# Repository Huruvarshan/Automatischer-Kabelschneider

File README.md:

# Automatischer Kabelschneider (Automatic Cable Cutter)

## Overview

The **Automatischer Kabelschneider** is an open-source, programmable device for automatically cutting cables and heat shrink tubes to precise lengths and quantities. Designed for makers, professionals, and hobbyists, it streamlines repetitive workshop tasks, ensuring accuracy, safety, and efficiency in cable and tube preparation.

This repository includes all hardware and software resources needed to build, assemble, and operate the device.

---

## Features

- **Programmable Length & Quantity:**  
  Set the desired length and number of pieces using capacitive buttons and an integrated display.

- **Precision Cutting:**  
  Delivers clean, accurate cuts suitable for various cable and tube diameters.

- **Material Flexibility:**  
  Supports cables, heat shrink tubes, and similar flexible materials.

- **Job Notification:**  
  Visual indicators (LEDs or beacons) signal job progress and completion.

- **Safety:**  
  Built-in overheat protection, a "SawStop"-style emergency system, and run-out sensors to prevent accidents.

---

## Repository Structure

```
Automatischer-Kabelschneider/
├── Hardware/
│   ├── PCB/           # KiCad PCB design files
│   ├── Mechanical/    # Mechanical design files (e.g., 3D models)
│   ├── BOM.md         # Bill of Materials
│   └── README.md      # Hardware documentation
├── Software/
│   ├── AKS_Program/   # Microcontroller firmware (ESP32)
│   │   └── README.md  # Software setup and usage
│   └── README.md      # Software structure and notes
├── Images/            # Project and schematic images
│   └── A6703971.JPG
└── README.md          # Project overview (this file)
```

---

## Getting Started

### 1. Hardware

- Manufacture and assemble the PCB and mechanical parts using files in `/Hardware`.
- Reference the Bill of Materials (`Hardware/BOM.md`) for required components.
- Follow detailed assembly instructions in `Hardware/README.md`.

### 2. Software

- The main firmware for the microcontroller (ESP32) is located in `Software/AKS_Program/`.
- See `Software/AKS_Program/README.md` for build, installation, and configuration steps.
- The firmware controls motors, sensors, and LED feedback, and communicates with the device interface.

### 3. Operation

- Use the device's capacitive interface to configure cut length and quantity.
- Start the automatic cutting process. LEDs provide real-time feedback.
- The machine stops automatically and alerts you when the job is complete.

---

## Documentation

- **Hardware Details:** [Hardware/README.md](Hardware/README.md)
- **Software Instructions:** [Software/AKS_Program/README.md](Software/AKS_Program/README.md)

---

## Contributing

Contributions, bug reports, and suggestions are welcome!  
Please open an issue or submit a pull request via GitHub.

---

## Safety & Disclaimer

- Always follow safety instructions and observe caution while operating the device.
- The authors are not responsible for any injury or damage resulting from use or misuse of this project.

---

## License

This project is licensed under the MIT License.  
See [LICENSE](LICENSE) for details.

---

**Let’s build better tools together!**

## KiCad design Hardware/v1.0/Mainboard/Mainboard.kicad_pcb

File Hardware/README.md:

# Hardware Documentation

Welcome to the hardware section of the Automatischer Kabelschneider (Automatic Cable Cutter) project.

## PCB Design

- The PCB (Printed Circuit Board) design files are available here:  
  [./PCB/](Automatischer-Kabelschneider/Hardware/PCB/)

## Mechanical Design

- The mechanical design files can be found here:  
  [./Mechanical/](../Mechanical/)  

## Bill of Materials (BOM)

- A complete list of components required for the hardware build is available here:  
  [./BOM.md](./BOM.md)  

## Assembly Instructions

- Step-by-step instructions for assembling the hardware will be provided here.  

## Firmware

- The firmware for running the device is located in the main repository:  
  [../Firmware/](../Firmware/)

## Additional Notes

- Please check that all the referenced files and folders are present in this directory.
- For troubleshooting, questions, or contributions, please open an issue in the main repository.

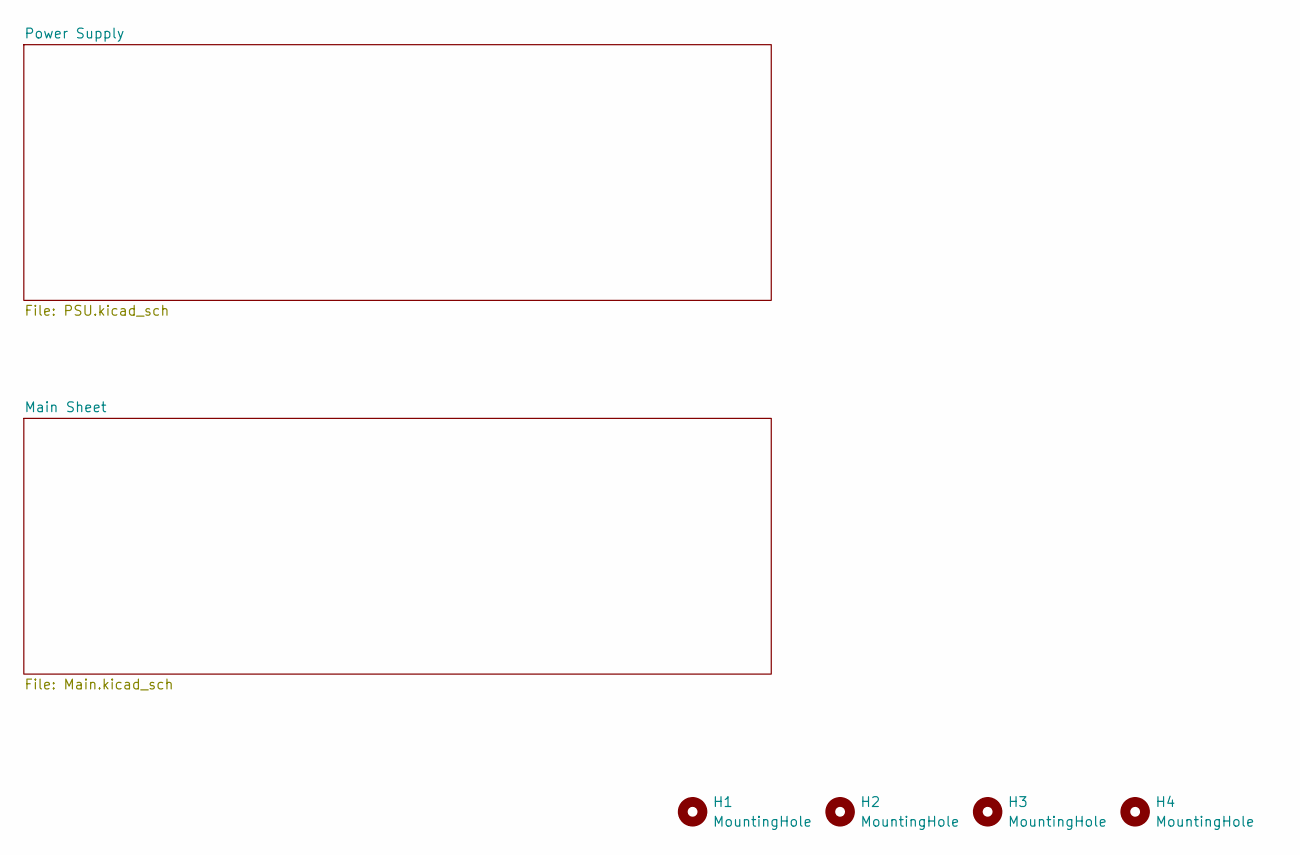
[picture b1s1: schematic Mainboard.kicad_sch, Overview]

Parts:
H1, H2, H3, H4: MountingHole; MountingHole_3.2mm_M3

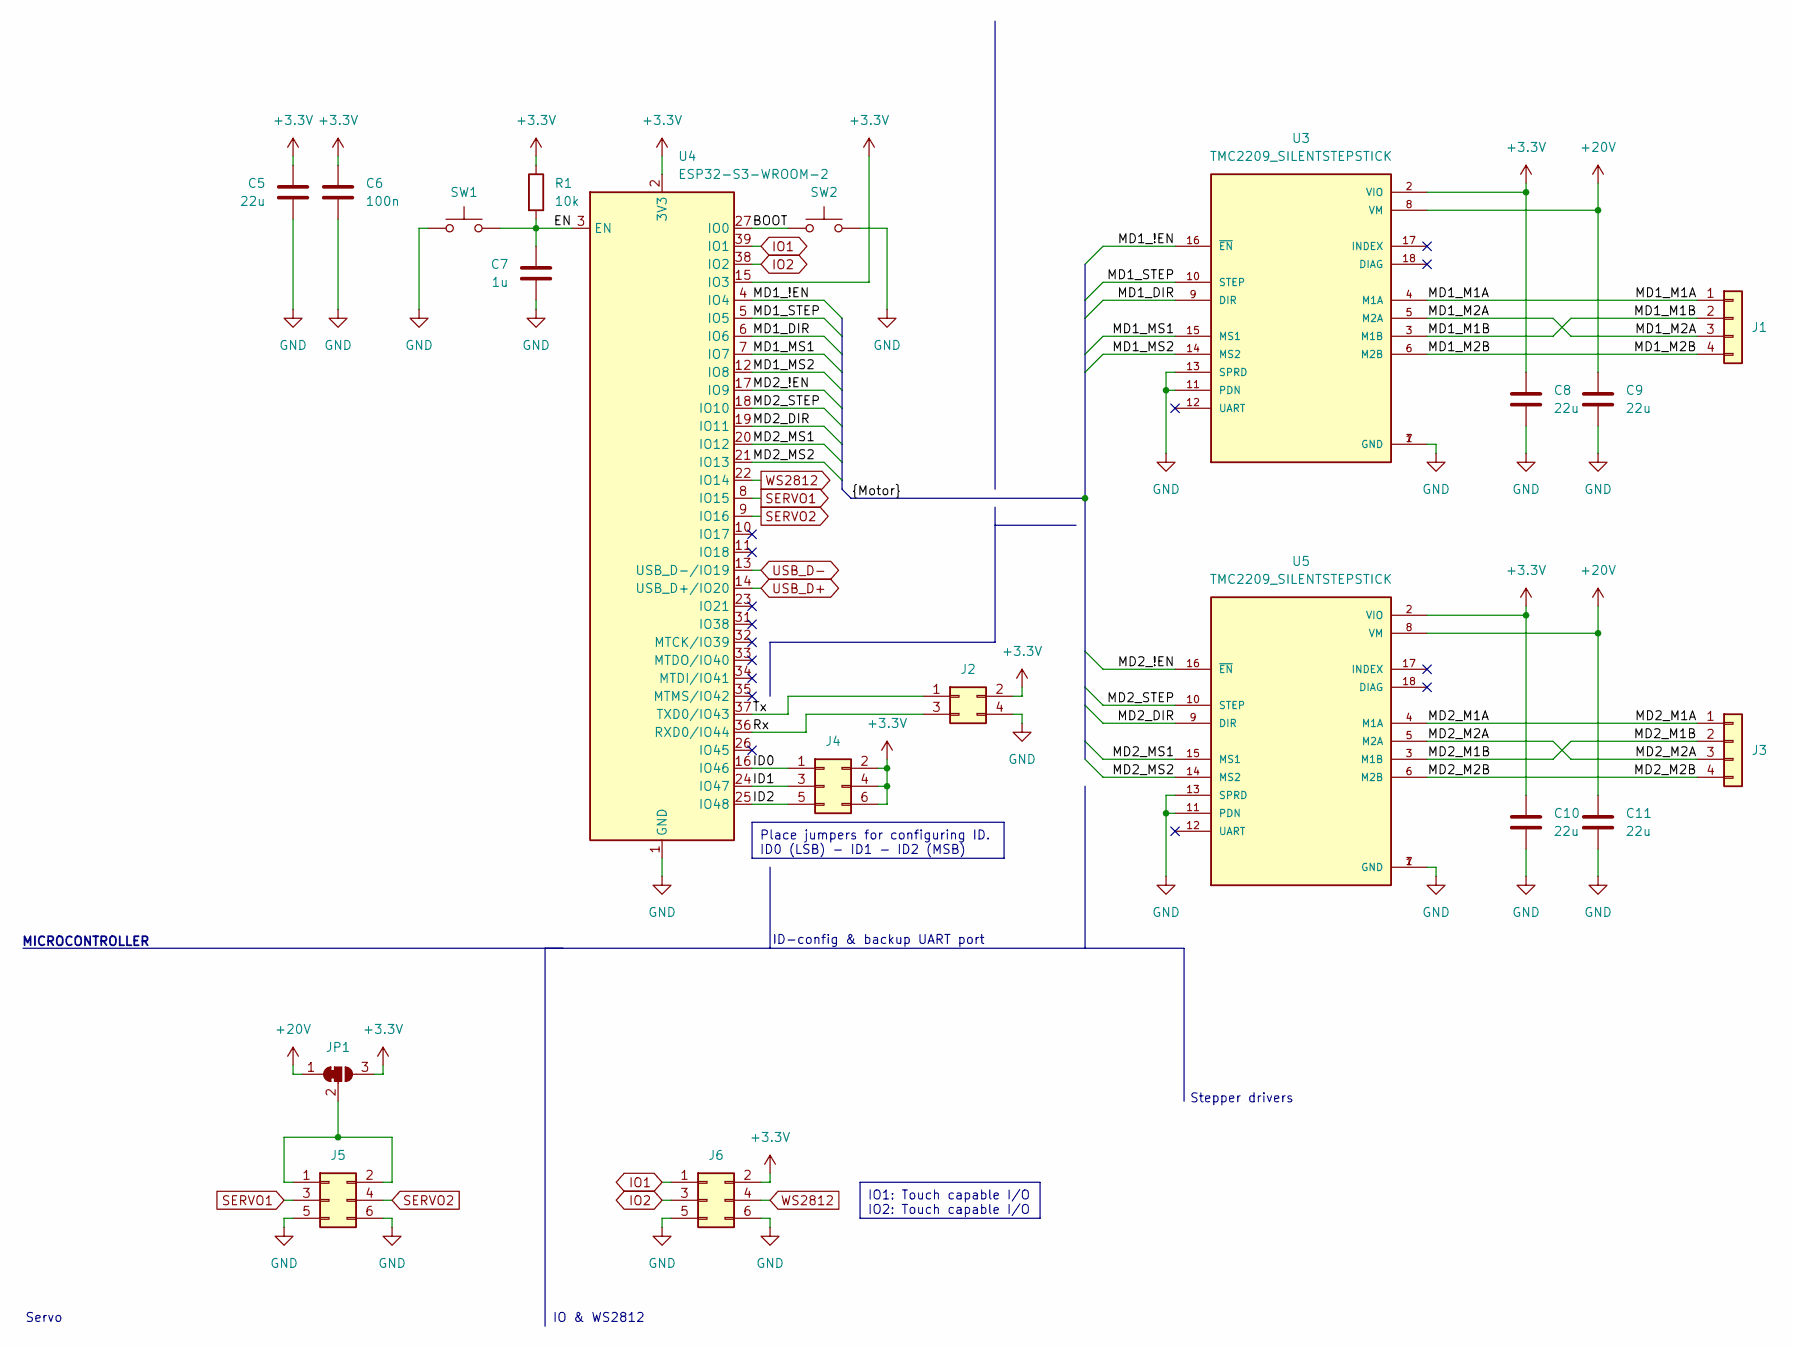
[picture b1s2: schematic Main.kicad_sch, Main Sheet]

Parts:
C5, C8, C9, C10, C11: 22u; C_0805_2012Metric
C6: 100n; C_0805_2012Metric
C7: 1u; C_0805_2012Metric
J1, J3: Conn_01x04; PhoenixContact_MC_1,5_4-G-3.81_1x04_P3.81mm_Horizontal
J2: Conn_02x02_Odd_Even; PinHeader_2x02_P2.54mm_Vertical
J4, J5, J6: Conn_02x03_Odd_Even; PinHeader_2x03_P2.54mm_Vertical
JP1: SolderJumper_3_Bridged12; SolderJumper-3_P1.3mm_Bridged12_RoundedPad1.0x1.5mm
R1: 10k; R_0805_2012Metric
SW1, SW2: SW_Push; SW_Push_1P1T_NO_6x6mm_H9.5mm
U3, U5: TMC2209_SILENTSTEPSTICK; MODULE_TMC2209_SILENTSTEPSTICK; PARTREV 1.20
U4: ESP32-S3-WROOM-2

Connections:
+3.3V: C5.1, C6.1, C8.1, C10.1, J2.2, J4.2, J4.4, J4.6, J6.2, JP1.3 (B), R1.1, U3.2 (VIO), U4.2 (3V3), U4.15 (IO3), U5.2 (VIO); also elsewhere on the board
+20V: C9.1, C11.1, JP1.1 (A), U3.8 (VM), U5.8 (VM); also elsewhere on the board
/Main Sheet/BOOT: SW2.1, U4.27 (IO0)
/Main Sheet/EN: C7.1, R1.2, SW1.2, U4.3 (EN)
/Main Sheet/ID0: J4.1, U4.16 (IO46)
/Main Sheet/ID1: J4.3, U4.24 (IO47)
/Main Sheet/ID2: J4.5, U4.25 (IO48)
/Main Sheet/MD1_!EN: U3.16 (~EN), U4.4 (IO4)
/Main Sheet/MD1_DIR: U3.9 (DIR), U4.6 (IO6)
/Main Sheet/MD1_M1A: J1.1, U3.4 (M1A)
/Main Sheet/MD1_M1B: J1.2, U3.3 (M1B)
/Main Sheet/MD1_M2A: J1.3, U3.5 (M2A)
/Main Sheet/MD1_M2B: J1.4, U3.6 (M2B)
/Main Sheet/MD1_MS1: U3.15 (MS1), U4.7 (IO7)
/Main Sheet/MD1_MS2: U3.14 (MS2), U4.12 (IO8)
/Main Sheet/MD1_STEP: U3.10 (STEP), U4.5 (IO5)
/Main Sheet/MD2_!EN: U4.17 (IO9), U5.16 (~EN)
/Main Sheet/MD2_DIR: U4.19 (IO11), U5.9 (DIR)
/Main Sheet/MD2_M1A: J3.1, U5.4 (M1A)
/Main Sheet/MD2_M1B: J3.2, U5.3 (M1B)
/Main Sheet/MD2_M2A: J3.3, U5.5 (M2A)
/Main Sheet/MD2_M2B: J3.4, U5.6 (M2B)
/Main Sheet/MD2_MS1: U4.20 (IO12), U5.15 (MS1)
/Main Sheet/MD2_MS2: U4.21 (IO13), U5.14 (MS2)
/Main Sheet/MD2_STEP: U4.18 (IO10), U5.10 (STEP)
/Main Sheet/Rx: J2.3, U4.36 (RXD0/IO44)
/Main Sheet/Tx: J2.1, U4.37 (TXD0/IO43)
GND: C5.2, C6.2, C7.2, C8.2, C9.2, C10.2, C11.2, J2.4, J5.5, J5.6, J6.5, J6.6, SW1.1, SW2.2, U3.1 (GND), U3.7 (GND), U3.11 (PDN), U3.13 (SPRD), U4.1 (GND), U4.40 (GND), U4.41 (GND), U5.1 (GND), U5.7 (GND), U5.11 (PDN), U5.13 (SPRD); also elsewhere on the board
IO1: J6.1, U4.39 (IO1)
IO2: J6.3, U4.38 (IO2)
unnamed: J5.1, J5.2, JP1.2 (C)
SERVO1: J5.3, U4.8 (IO15)
SERVO2: J5.4, U4.9 (IO16)
USB_D+: U4.14 (USB_D+/IO20); also elsewhere on the board
USB_D-: U4.13 (USB_D-/IO19); also elsewhere on the board
WS2812: J6.4, U4.22 (IO14)

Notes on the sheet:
IO1: Touch capable I/O IO2: Touch capable I/O
Place jumpers for configuring ID. ID0 (LSB) - ID1 - ID2 (MSB)
IO & WS2812
Stepper drivers
Servo
ID-config & backup UART port
MICROCONTROLLER

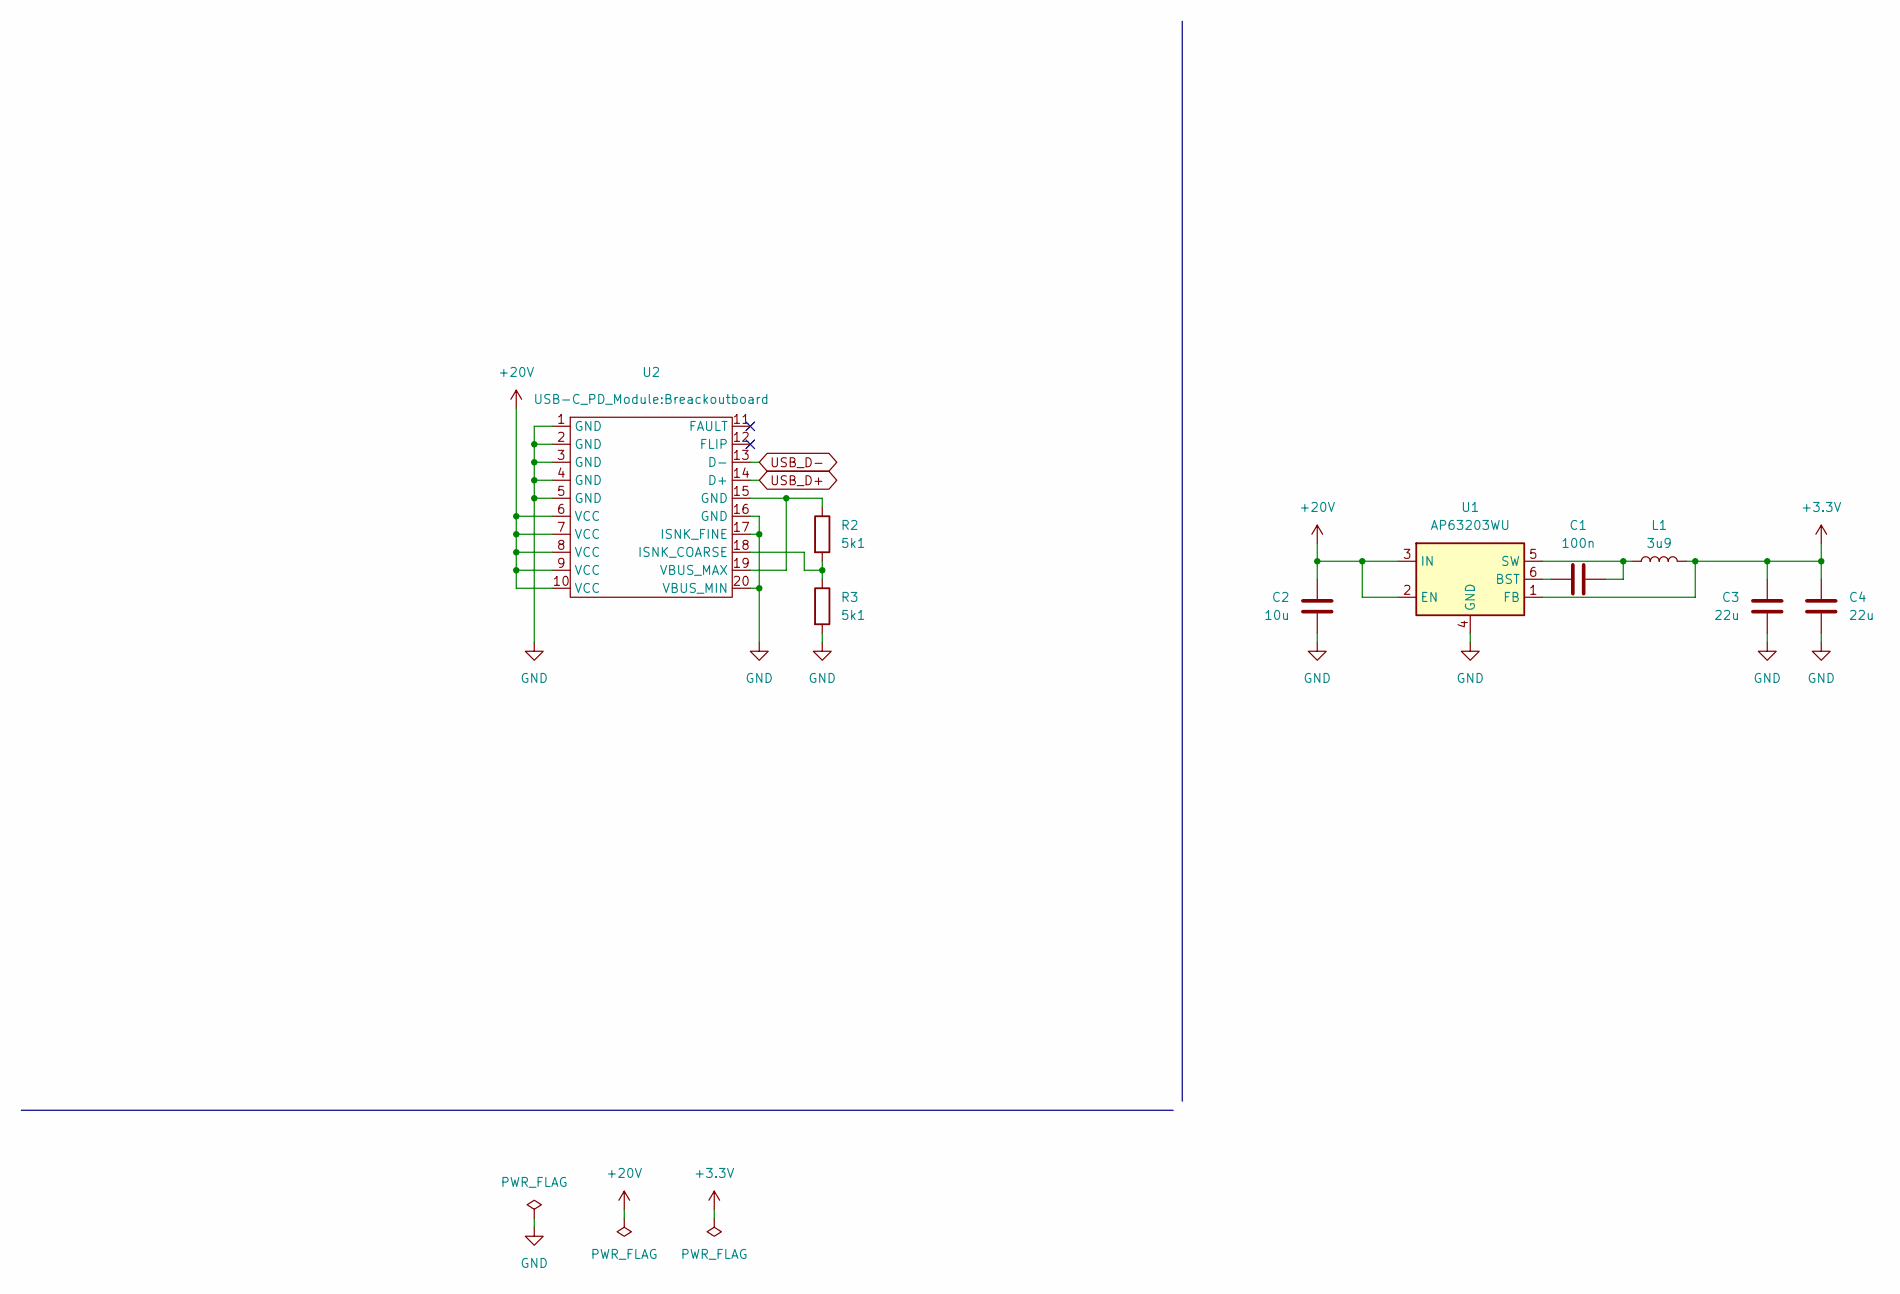
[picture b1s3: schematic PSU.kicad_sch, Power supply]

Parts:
C1: 100n; C_0805_2012Metric
C2: 10u; C_0805_2012Metric
C3, C4: 22u; C_0805_2012Metric
L1: 3u9; L_Wurth_WE-LQSH-4020
R2, R3: 5k1; R_0805_2012Metric
U1: AP63203WU; TSOT-23-6
U2: Breackoutboard

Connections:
+3.3V: C3.1, C4.1, L1.2, U1.1 (FB); also elsewhere on the board
+20V: C2.1, U1.2 (EN), U1.3 (IN), U2.6 (VCC), U2.7 (VCC), U2.8 (VCC), U2.9 (VCC), U2.10 (VCC); also elsewhere on the board
GND: C2.2, C3.2, C4.2, R3.2, U1.4 (GND), U2.1 (GND), U2.2 (GND), U2.3 (GND), U2.4 (GND), U2.5 (GND), U2.16 (GND), U2.17 (ISNK_FINE), U2.20 (VBUS_MIN); also elsewhere on the board
unnamed: C1.2, U1.6 (BST)
unnamed: C1.1, L1.1, U1.5 (SW)
unnamed: R2.2, R3.1, U2.18 (ISNK_COARSE)
unnamed: R2.1, U2.15 (GND), U2.19 (VBUS_MAX)
USB_D+: U2.14 (D+); also elsewhere on the board
USB_D-: U2.13 (D-); also elsewhere on the board

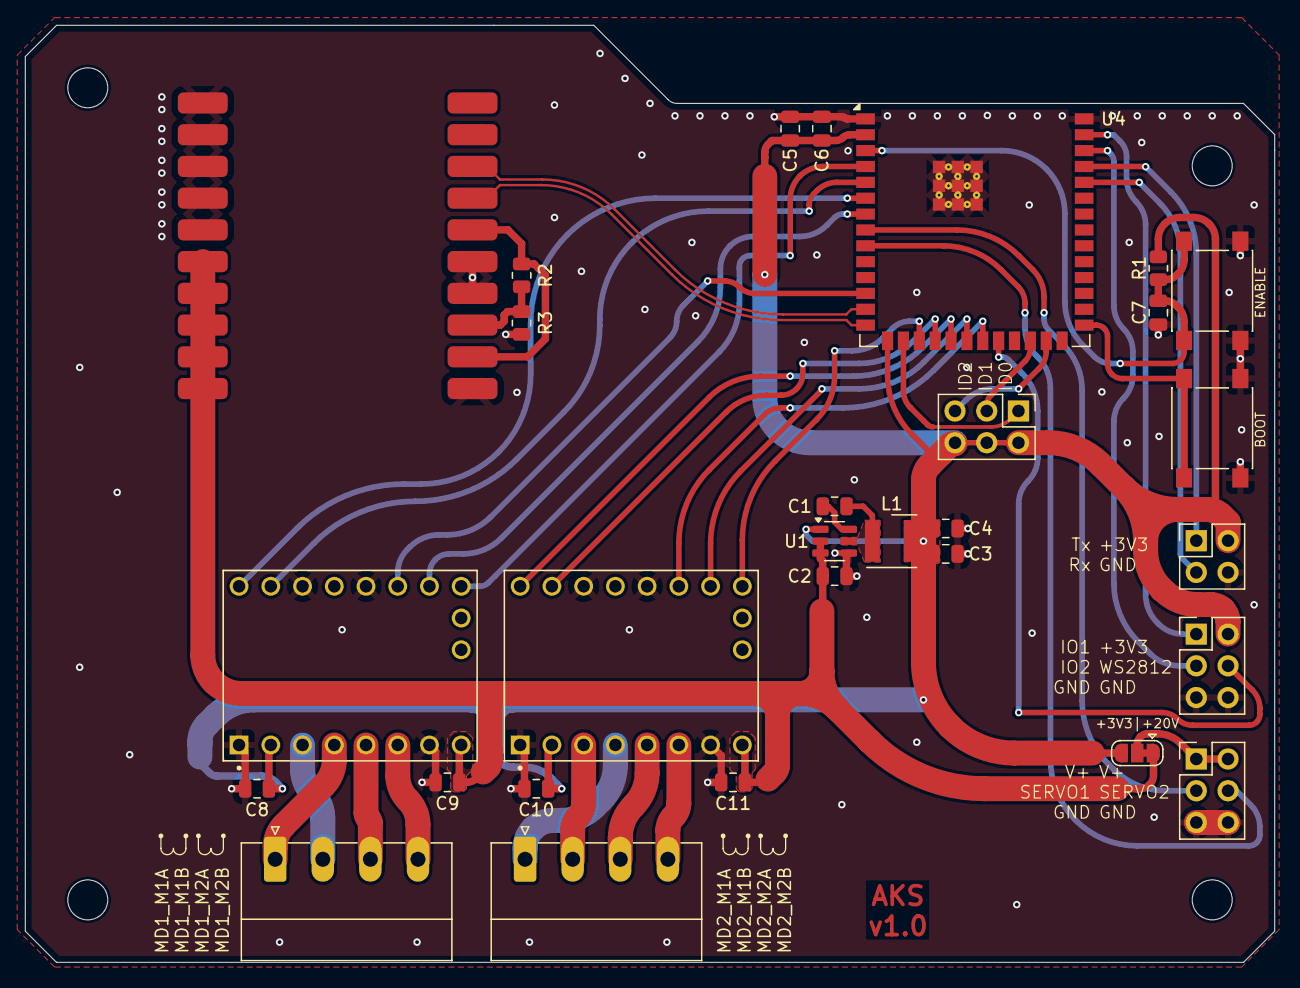
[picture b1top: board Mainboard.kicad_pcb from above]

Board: 2 copper layers, 100.0 x 75.0 mm, 33 parts (0 on the bottom side), 40 nets.

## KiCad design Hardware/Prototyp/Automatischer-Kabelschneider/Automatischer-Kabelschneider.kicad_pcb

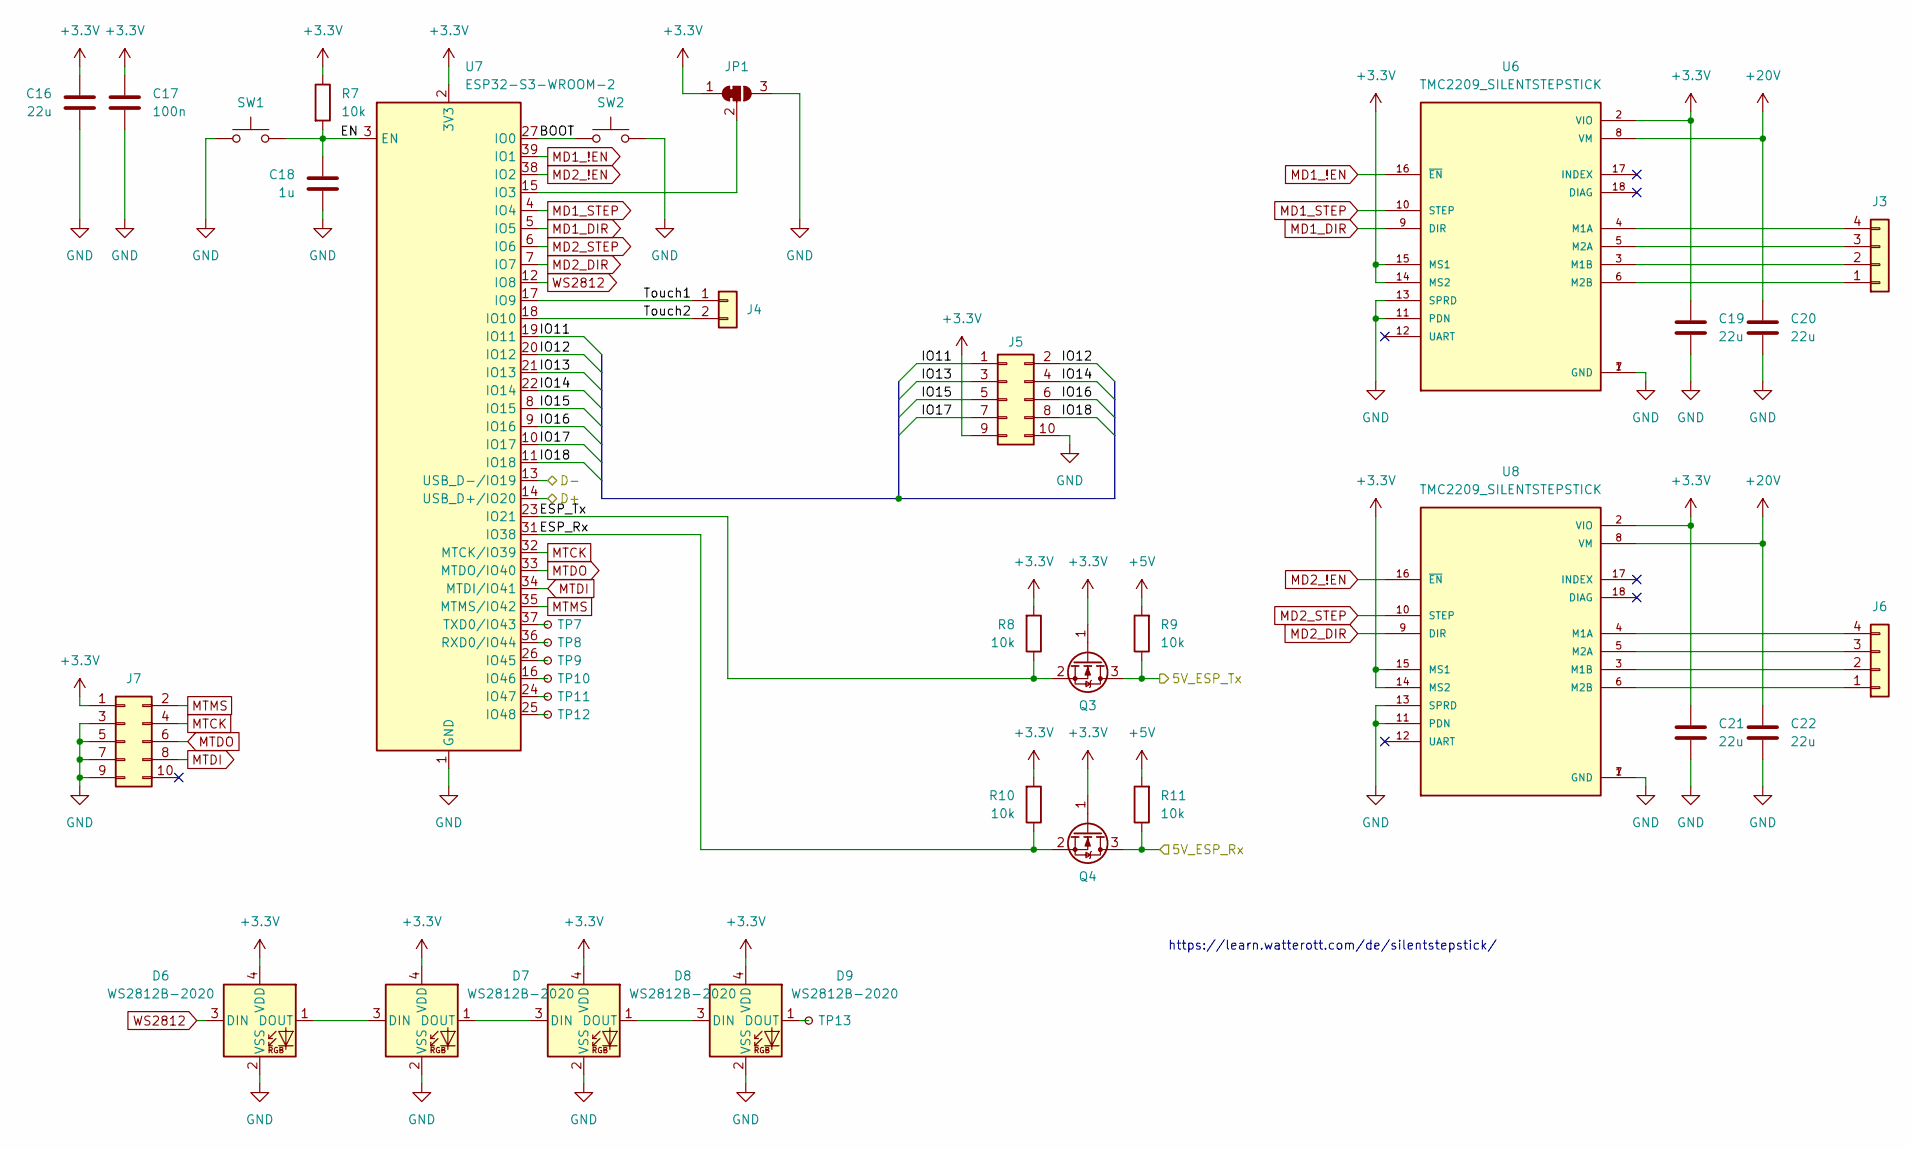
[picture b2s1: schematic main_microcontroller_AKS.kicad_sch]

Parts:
C16, C19, C20, C21, C22: 22u; C_0805_2012Metric
C17: 100n; C_0805_2012Metric
C18: 1u; C_0805_2012Metric
D6, D7, D8, D9: WS2812B-2020; LED_WS2812B-2020_PLCC4_2.0x2.0mm
J3, J6: Conn_01x04; PhoenixContact_GMSTBA_2,5_4-G-7,62_1x04_P7.62mm_Horizontal
J4: Conn_01x02; SolderWire-1.5sqmm_1x02_P6mm_D1.7mm_OD3mm_Relief
J5: Conn_02x05_Odd_Even; IDC-Header_2x05_P2.54mm_Vertical
J7: Conn_02x05_Odd_Even; PinHeader_2x05_P1.27mm_Vertical
JP1: SolderJumper_3_Bridged12; SolderJumper-3_P1.3mm_Bridged12_RoundedPad1.0x1.5mm
Q3, Q4: Q_NMOS_GSD; TSOT-23
R7, R8, R9, R10, R11: 10k; R_0805_2012Metric
SW1, SW2: SW_Push; SW_Push_1P1T_NO_6x6mm_H9.5mm
TP7, TP8, TP9, TP10, TP11, TP12, TP13: TestPoint_Small; TestPoint_Pad_D1.0mm
U6, U8: TMC2209_SILENTSTEPSTICK; MODULE_TMC2209_SILENTSTEPSTICK; PARTREV 1.20
U7: ESP32-S3-WROOM-2

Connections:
+3.3V: C16.1, C17.1, C19.1, C21.1, D6.4 (VDD), D7.4 (VDD), D8.4 (VDD), D9.4 (VDD), J5.9, J7.1, JP1.1 (A), Q3.1 (G), Q4.1 (G), R7.1, R8.2, R10.2, U6.2 (VIO), U6.14 (MS2), U6.15 (MS1), U7.2 (3V3), U8.2 (VIO), U8.14 (MS2), U8.15 (MS1); also elsewhere on the board
+5V: R9.2, R11.2; also elsewhere on the board
+20V: C20.1, C22.1, U6.8 (VM), U8.8 (VM); also elsewhere on the board
/Main Microcontroller/BOOT: SW2.1, U7.27 (IO0)
/Main Microcontroller/D+: U7.14 (USB_D+/IO20); also elsewhere on the board
/Main Microcontroller/D-: U7.13 (USB_D-/IO19); also elsewhere on the board
/Main Microcontroller/EN: C18.1, R7.2, SW1.2, U7.3 (EN)
/Main Microcontroller/ESP_Rx: Q4.2 (S), R10.1, U7.31 (IO38)
/Main Microcontroller/ESP_Tx: Q3.2 (S), R8.1, U7.23 (IO21)
/Main Microcontroller/IO11: J5.1, U7.19 (IO11)
/Main Microcontroller/IO12: J5.2, U7.20 (IO12)
/Main Microcontroller/IO13: J5.3, U7.21 (IO13)
/Main Microcontroller/IO14: J5.4, U7.22 (IO14)
/Main Microcontroller/IO15: J5.5, U7.8 (IO15)
/Main Microcontroller/IO16: J5.6, U7.9 (IO16)
/Main Microcontroller/IO17: J5.7, U7.10 (IO17)
/Main Microcontroller/IO18: J5.8, U7.11 (IO18)
/Main Microcontroller/Touch1: J4.1, U7.17 (IO9)
/Main Microcontroller/Touch2: J4.2, U7.18 (IO10)
/Slave Microcontroller/ATMEGA_Rx: Q3.3 (D), R9.1; also elsewhere on the board
/Slave Microcontroller/ATMEGA_Tx: Q4.3 (D), R11.1; also elsewhere on the board
GND: C16.2, C17.2, C18.2, C19.2, C20.2, C21.2, C22.2, D6.2 (VSS), D7.2 (VSS), D8.2 (VSS), D9.2 (VSS), J5.10, J7.3, J7.5, J7.7, J7.9, JP1.3 (B), SW1.1, SW2.2, U6.1 (GND), U6.7 (GND), U6.11 (PDN), U6.13 (SPRD), U7.1 (GND), U7.40 (GND), U7.41 (GND), U8.1 (GND), U8.7 (GND), U8.11 (PDN), U8.13 (SPRD); also elsewhere on the board
MD1_!EN: U6.16 (~EN), U7.39 (IO1)
MD1_DIR: U6.9 (DIR), U7.5 (IO5)
MD1_STEP: U6.10 (STEP), U7.4 (IO4)
MD2_!EN: U7.38 (IO2), U8.16 (~EN)
MD2_DIR: U7.7 (IO7), U8.9 (DIR)
MD2_STEP: U7.6 (IO6), U8.10 (STEP)
MTCK: J7.4, U7.32 (MTCK/IO39)
MTDI: J7.8, U7.34 (MTDI/IO41)
MTDO: J7.6, U7.33 (MTDO/IO40)
MTMS: J7.2, U7.35 (MTMS/IO42)
unnamed: D6.1 (DOUT), D7.3 (DIN)
unnamed: D7.1 (DOUT), D8.3 (DIN)
unnamed: D8.1 (DOUT), D9.3 (DIN)
unnamed: D9.1 (DOUT), TP13.1
unnamed: J3.1, U6.6 (M2B)
unnamed: J3.2, U6.3 (M1B)
unnamed: J3.3, U6.5 (M2A)
unnamed: J3.4, U6.4 (M1A)
unnamed: J6.1, U8.6 (M2B)
unnamed: J6.2, U8.3 (M1B)
unnamed: J6.3, U8.5 (M2A)
unnamed: J6.4, U8.4 (M1A)
unnamed: JP1.2 (C), U7.15 (IO3)
unnamed: TP9.1, U7.26 (IO45)
unnamed: TP10.1, U7.16 (IO46)
unnamed: TP11.1, U7.24 (IO47)
unnamed: TP12.1, U7.25 (IO48)
unnamed: TP8.1, U7.36 (RXD0/IO44)
unnamed: TP7.1, U7.37 (TXD0/IO43)
WS2812: D6.3 (DIN), U7.12 (IO8)

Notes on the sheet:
https://learn.watterott.com/de/silentstepstick/

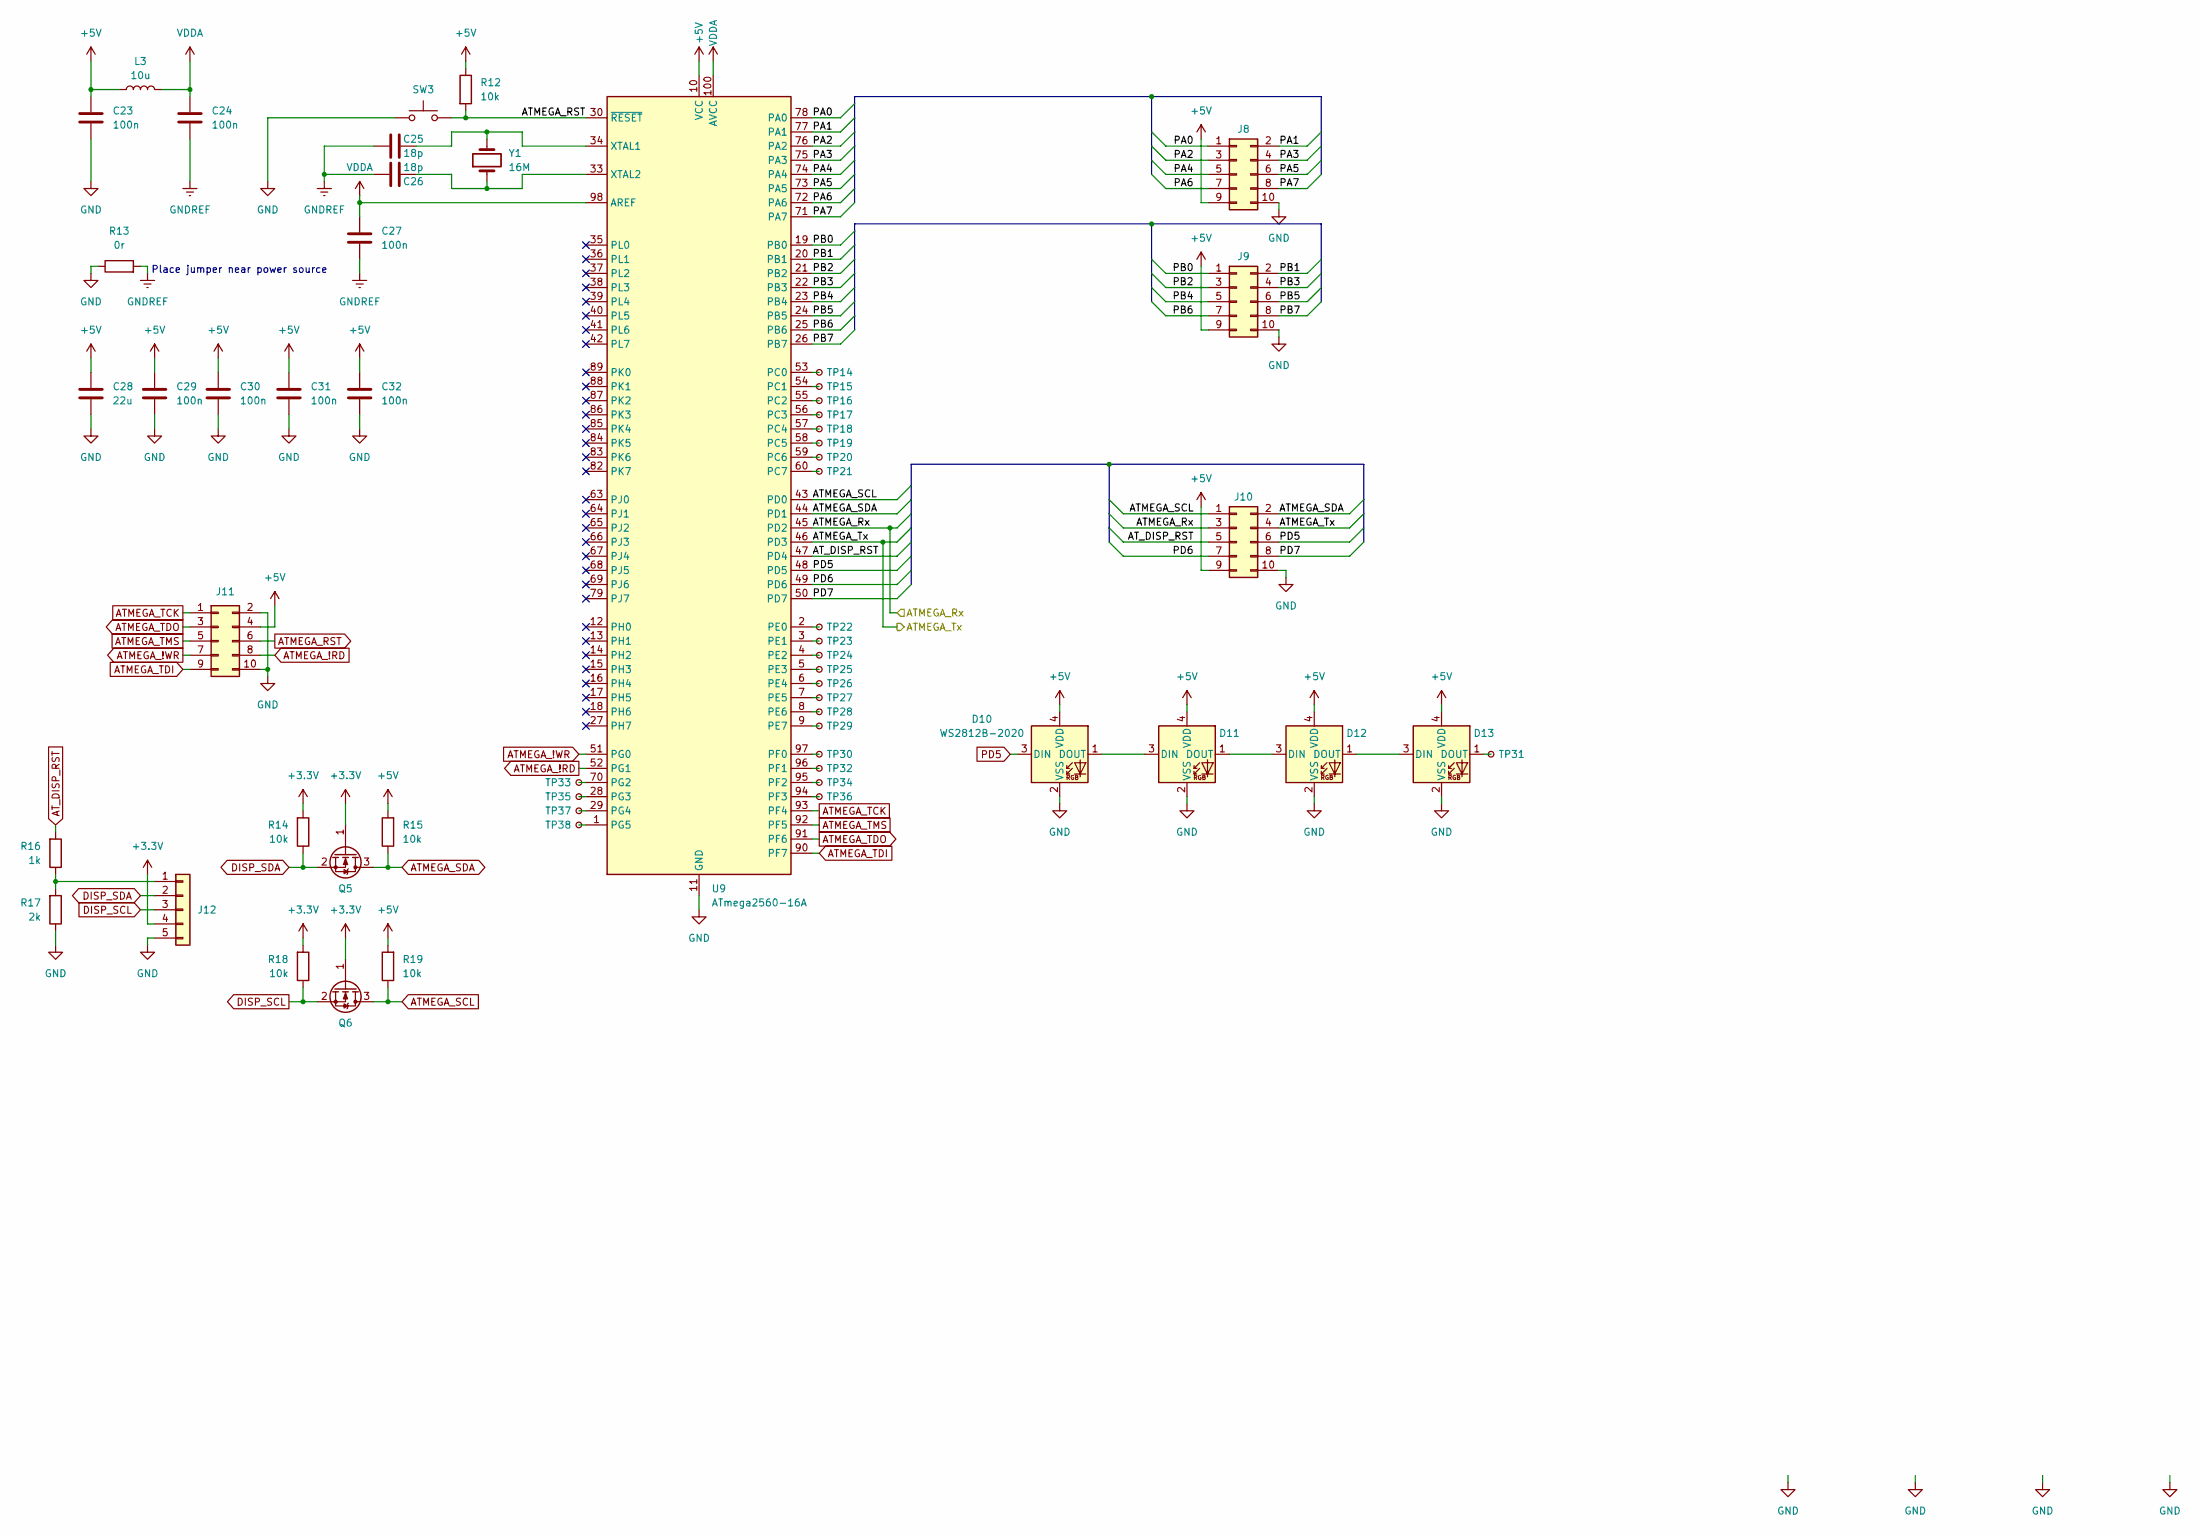
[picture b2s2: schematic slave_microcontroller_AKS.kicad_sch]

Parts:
C23, C24, C27, C29, C30, C31, C32: 100n; C_0805_2012Metric
C25, C26: 18p; C_0805_2012Metric
C28: 22u; C_0805_2012Metric
D10, D11, D12, D13: WS2812B-2020; LED_WS2812B-2020_PLCC4_2.0x2.0mm
J8, J9, J10: Conn_02x05_Odd_Even; IDC-Header_2x05_P2.54mm_Vertical
J11: Conn_02x05_Odd_Even; PinHeader_2x05_P1.27mm_Vertical
J12: Conn_01x05; PinHeader_1x05_P2.54mm_Vertical
L3: 10u; L_0805_2012Metric
Q5, Q6: Q_NMOS_GSD; TSOT-23
R12, R14, R15, R18, R19: 10k; R_0805_2012Metric
R13: 0r; R_0805_2012Metric
R16: 1k; R_0805_2012Metric
R17: 2k; R_0805_2012Metric
SW3: SW_Push; SW_Push_1P1T_NO_6x6mm_H9.5mm
TP14, TP15, TP16, TP17, TP18, TP19, TP20, TP21, TP22, TP23, TP24, TP25, TP26, TP27, TP28, TP29, TP30, TP31, TP32, TP33, TP34, TP35, TP36, TP37, TP38: TestPoint_Small; TestPoint_Pad_D1.0mm
U9: ATmega2560-16A; TQFP-100_14x14mm_P0.5mm
Y1: 16M; Crystal_SMD_ECS_CSM3X-2Pin_7.6x4.1mm

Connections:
+3.3V: J12.4, Q5.1 (G), Q6.1 (G), R14.2, R18.2; also elsewhere on the board
+5V: C23.1, C28.1, C29.1, C30.1, C31.1, C32.1, D10.4 (VDD), D11.4 (VDD), D12.4 (VDD), D13.4 (VDD), J8.9, J9.9, J10.9, J11.4, L3.1, R12.1, R15.2, R19.2, U9.10 (VCC), U9.31 (VCC), U9.61 (VCC), U9.80 (VCC); also elsewhere on the board
/Slave Microcontroller/ATMEGA_Rx: J10.3, U9.45 (PD2); also elsewhere on the board
/Slave Microcontroller/ATMEGA_Tx: J10.4, U9.46 (PD3); also elsewhere on the board
/Slave Microcontroller/PA0: J8.1, U9.78 (PA0)
/Slave Microcontroller/PA1: J8.2, U9.77 (PA1)
/Slave Microcontroller/PA2: J8.3, U9.76 (PA2)
/Slave Microcontroller/PA3: J8.4, U9.75 (PA3)
/Slave Microcontroller/PA4: J8.5, U9.74 (PA4)
/Slave Microcontroller/PA5: J8.6, U9.73 (PA5)
/Slave Microcontroller/PA6: J8.7, U9.72 (PA6)
/Slave Microcontroller/PA7: J8.8, U9.71 (PA7)
/Slave Microcontroller/PB0: J9.1, U9.19 (PB0)
/Slave Microcontroller/PB1: J9.2, U9.20 (PB1)
/Slave Microcontroller/PB2: J9.3, U9.21 (PB2)
/Slave Microcontroller/PB3: J9.4, U9.22 (PB3)
/Slave Microcontroller/PB4: J9.5, U9.23 (PB4)
/Slave Microcontroller/PB5: J9.6, U9.24 (PB5)
/Slave Microcontroller/PB6: J9.7, U9.25 (PB6)
/Slave Microcontroller/PB7: J9.8, U9.26 (PB7)
/Slave Microcontroller/PD6: J10.7, U9.49 (PD6)
/Slave Microcontroller/PD7: J10.8, U9.50 (PD7)
ATMEGA_!RD: J11.8, U9.52 (PG1)
ATMEGA_!WR: J11.7, U9.51 (PG0)
ATMEGA_RST: J11.6, R12.2, SW3.2, U9.30 (~RESET)
ATMEGA_SCL: J10.1, Q6.3 (D), R19.1, U9.43 (PD0)
ATMEGA_SDA: J10.2, Q5.3 (D), R15.1, U9.44 (PD1)
ATMEGA_TCK: J11.1, U9.93 (PF4)
ATMEGA_TDI: J11.9, U9.90 (PF7)
ATMEGA_TDO: J11.3, U9.91 (PF6)
ATMEGA_TMS: J11.5, U9.92 (PF5)
AT_DISP_RST: J10.5, R16.2, U9.47 (PD4)
DISP_SCL: J12.3, Q6.2 (S), R18.1
DISP_SDA: J12.2, Q5.2 (S), R14.1
GND: C23.2, C28.2, C29.2, C30.2, C31.2, C32.2, D10.2 (VSS), D11.2 (VSS), D12.2 (VSS), D13.2 (VSS), J8.10, J9.10, J10.10, J11.2, J11.10, J12.5, R13.1, R17.1, SW3.1, U9.11 (GND), U9.32 (GND), U9.62 (GND), U9.81 (GND), U9.99 (GND); also elsewhere on the board
GNDREF: C24.2, C25.1, C26.1, C27.2, R13.2
unnamed: D10.1 (DOUT), D11.3 (DIN)
unnamed: D11.1 (DOUT), D12.3 (DIN)
unnamed: D12.1 (DOUT), D13.3 (DIN)
unnamed: D13.1 (DOUT), TP31.1
unnamed: J12.1, R16.1, R17.2
unnamed: TP14.1, U9.53 (PC0)
unnamed: TP15.1, U9.54 (PC1)
unnamed: TP16.1, U9.55 (PC2)
unnamed: TP17.1, U9.56 (PC3)
unnamed: TP18.1, U9.57 (PC4)
unnamed: TP19.1, U9.58 (PC5)
unnamed: TP20.1, U9.59 (PC6)
unnamed: TP21.1, U9.60 (PC7)
unnamed: TP22.1, U9.2 (PE0)
unnamed: TP23.1, U9.3 (PE1)
unnamed: TP24.1, U9.4 (PE2)
unnamed: TP25.1, U9.5 (PE3)
unnamed: TP26.1, U9.6 (PE4)
unnamed: TP27.1, U9.7 (PE5)
unnamed: TP28.1, U9.8 (PE6)
unnamed: TP29.1, U9.9 (PE7)
unnamed: TP30.1, U9.97 (PF0)
unnamed: TP32.1, U9.96 (PF1)
unnamed: TP34.1, U9.95 (PF2)
unnamed: TP36.1, U9.94 (PF3)
unnamed: TP33.1, U9.70 (PG2)
unnamed: TP35.1, U9.28 (PG3)
unnamed: TP37.1, U9.29 (PG4)
unnamed: TP38.1, U9.1 (PG5)
unnamed: C25.2, U9.34 (XTAL1), Y1.2
unnamed: C26.2, U9.33 (XTAL2), Y1.1
PD5: D10.3 (DIN), J10.6, U9.48 (PD5)
VDDA: C24.1, C27.1, L3.2, U9.98 (AREF), U9.100 (AVCC)

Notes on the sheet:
Place jumper near power source
